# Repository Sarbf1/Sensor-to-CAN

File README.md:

# Sensor-to-CAN
A HAT for Arduino nano, to Connect nearly any sensor and send its walues using CAN or NMEA bus

This is an early version. The hardware is drwan, but not checked or tested.
The four layer board is slightly larger than the arduino nano R4, as i have added a shield ring (in case of use in high EMV areas such as in electric vehicles).

Also the code has not been written yet, but will follow.

The goal is to have a HAT board for on a Arduino Nano R4, that can connect to any sensor (3.3V 500mA, 5V 1A or Vin).
The sensor vaule (any voltage, or current input, selectable with a jumper) is processed by the arduino R4 and the sent using CANbus, using NMEA2000 protocol.
It has three LEDs that can be configured (currentls intended to show TX, RX and Erros) and two buttons, of wich one is used as Arduino Reset.

## next steps
- [ ] build and test prototype
- [ ] Prgram Arduino R4
- [ ] implement CAN and NMEA200
- [ ] create Bill of material
- [ ] Make second physical prototype

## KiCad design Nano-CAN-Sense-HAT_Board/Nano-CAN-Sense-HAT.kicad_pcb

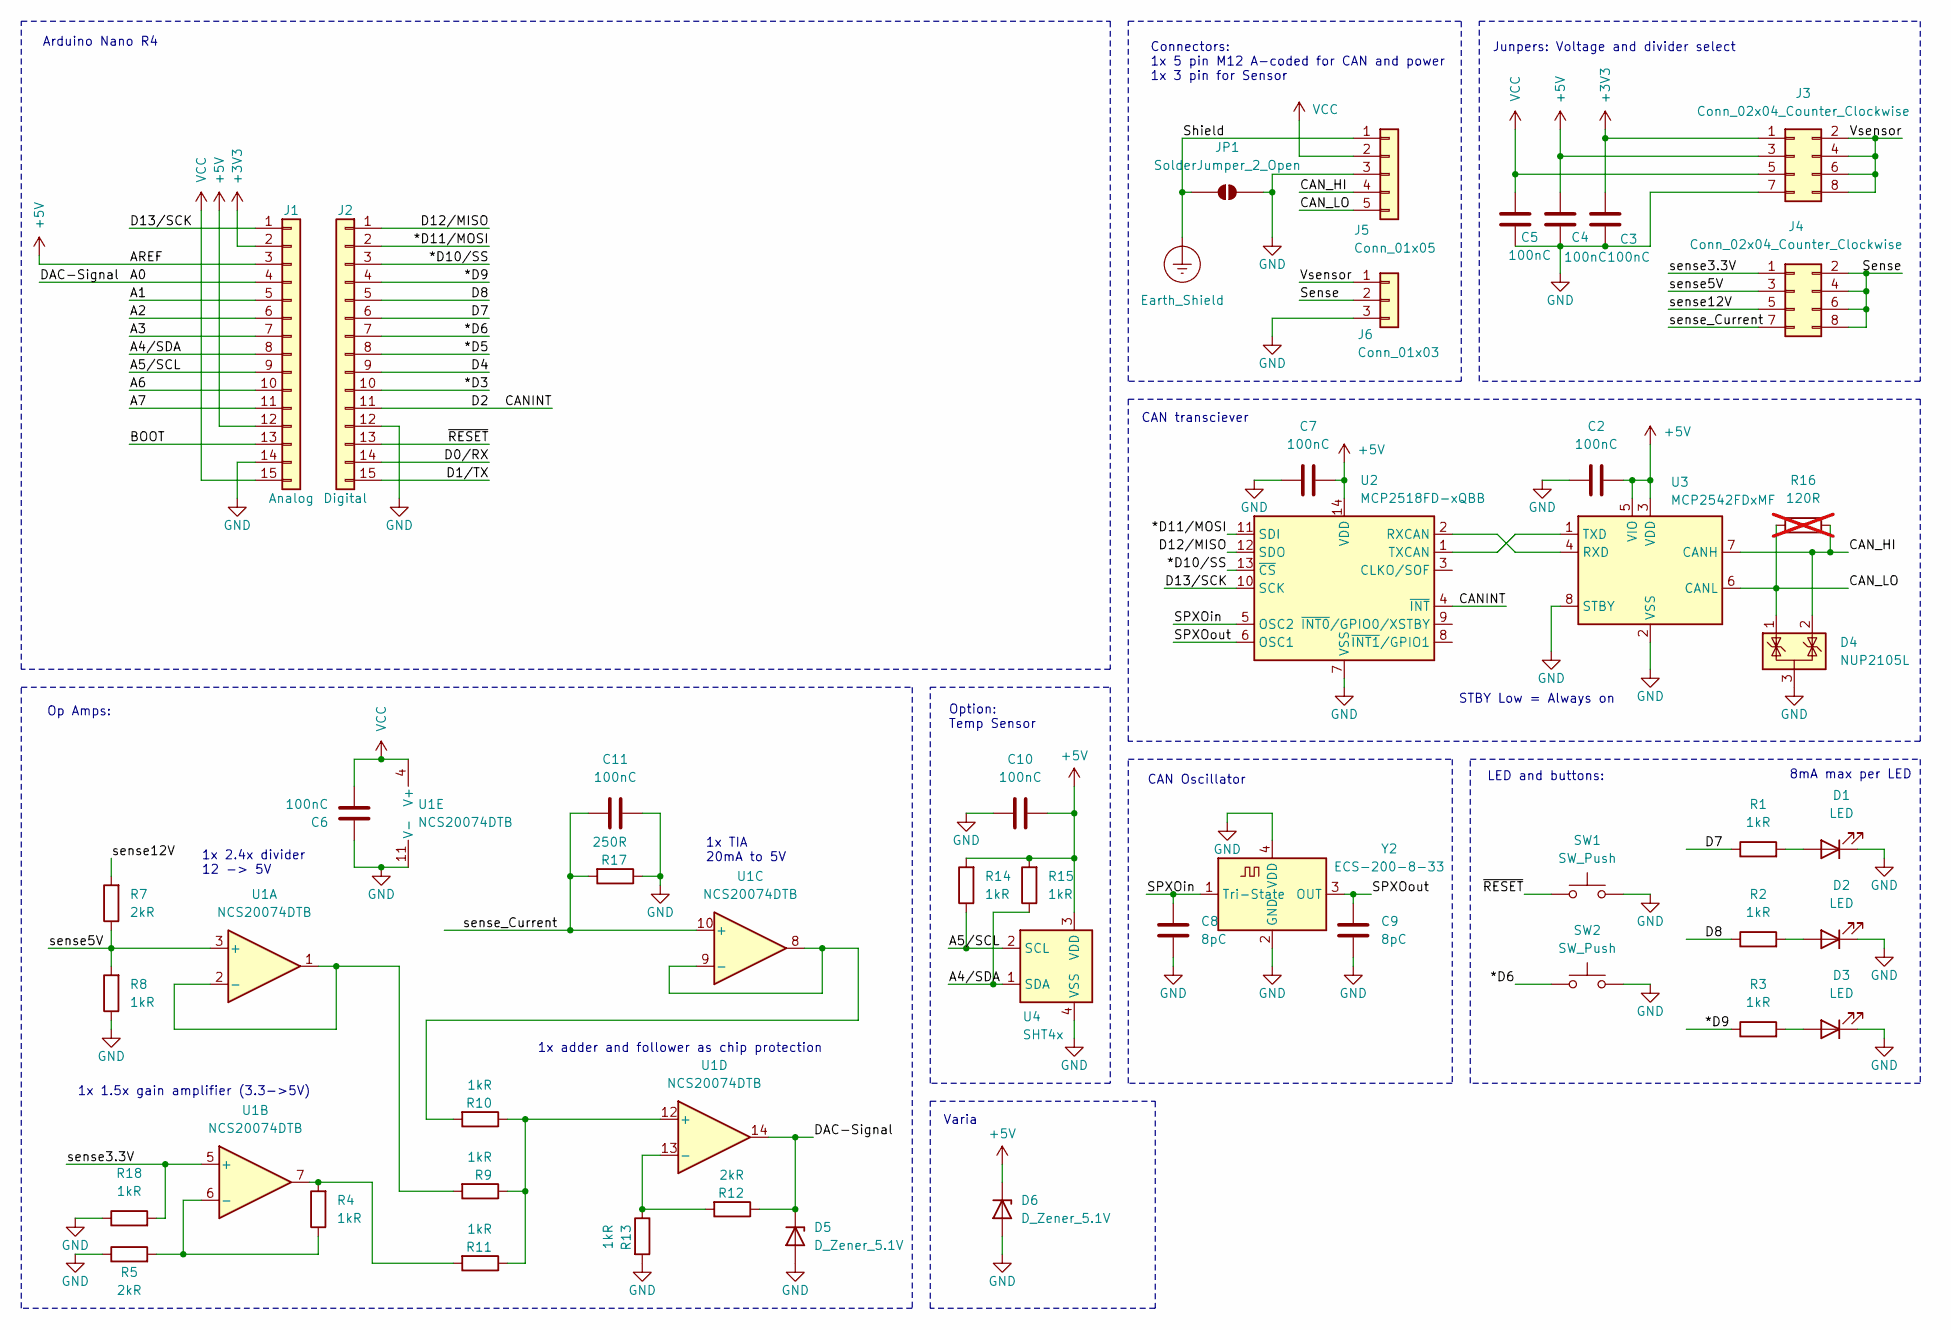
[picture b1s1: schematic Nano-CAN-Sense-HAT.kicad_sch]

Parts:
C2, C3, C4, C5, C6, C7, C10, C11: 100nC; C_0603_1608Metric
C8, C9: 8pC; C_0603_1608Metric
D1, D2, D3: LED; LED_0805_2012Metric
D4: NUP2105L; SOT-23
D5, D6: D_Zener_5.1V; D_SOD-323
J1: Analog; PinHeader_1x15_P2.54mm_Vertical
J2: Digital; PinHeader_1x15_P2.54mm_Vertical
J3, J4: Conn_02x04_Counter_Clockwise; PinHeader_2x04_P2.54mm_Vertical_SMD
J5: Conn_01x05; PinHeader_1x05_P2.54mm_Horizontal
J6: Conn_01x03; PinHeader_1x03_P2.54mm_Horizontal
JP1: SolderJumper_2_Open; SolderJumper-2_P1.3mm_Open_TrianglePad1.0x1.5mm
R1, R2, R3, R4, R8, R9, R10, R11, R13, R14, R15, R18: 1kR; R_0603_1608Metric
R5, R7, R12: 2kR; R_0603_1608Metric
R16: 120R; R_0603_1608Metric; not fitted
R17: 250R; R_0603_1608Metric
SW1, SW2: SW_Push; SW_SPST_B3U-1000P
U1: NCS20074DTB; TSSOP-14_4.4x5mm_P0.65mm
U2: MCP2518FD-xQBB; DFN-14-1EP_3x4.5mm_P0.65mm_EP1.65x4.25mm
U3: MCP2542FDxMF; DFN-8-1EP_3x3mm_P0.65mm_EP1.55x2.4mm
U4: SHT4x; Sensirion_DFN-4_1.5x1.5mm_P0.8mm_SHT4x_NoCentralPad
Y2: ECS-200-8-33; Oscillator_SMD_ECS_2520MV-xxx-xx-4Pin_2.5x2.0mm

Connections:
+3V3: C3.1, J1.2, J3.1
+5V: C2.2, C4.1, C7.2, C10.2, D6.1 (K), J1.3, J1.12, J3.3, R14.2, R15.2, U2.14 (VDD), U3.3 (VDD), U3.5 (VIO), U4.3 (VDD)
/*D3: J2.10
/*D5: J2.8
/*D6: J2.7, SW2.1
/*D9: J2.4, R3.1
/*D10/SS: J2.3, U2.13 (~CS)
/*D11/MOSI: J2.2, U2.11 (SDI)
/A0: D5.1 (K), J1.4, R12.1, U1.14
/A1: J1.5
/A2: J1.6
/A3: J1.7
/A4/SDA: J1.8, R15.1, U4.1 (SDA)
/A5/SCL: J1.9, R14.1, U4.2 (SCL)
/A6: J1.10
/A7: J1.11
/BOOT: J1.13
/CANINT: J2.11, U2.4 (~INT)
/CAN_HI: D4.2 (K), J5.4, R16.1, U3.7 (CANH)
/CAN_LO: D4.1 (K), J5.5, R16.2, U3.6 (CANL)
/D0/RX: J2.14
/D1/TX: J2.15
/D4: J2.9
/D7: J2.6, R1.1
/D8: J2.5, R2.1
/D12/MISO: J2.1, U2.12 (SDO)
/D13/SCK: J1.1, U2.10 (SCK)
/SPXOin: C8.2, U2.5 (OSC2), Y2.1 (Tri-State)
/SPXOout: C9.2, U2.6 (OSC1), Y2.3 (OUT)
/Sense: J4.2, J4.4, J4.6, J4.8, J6.2
/Vsensor: J3.2, J3.4, J3.6, J3.8, J6.1
/sense3.3V: J4.1, R18.2, U1.5 (+)
/sense5V: J4.3, R7.1, R8.2, U1.3 (+)
/sense12V: J4.5, R7.2
/sense_Current: C11.1, J4.7, R17.2, U1.10 (+)
/~RESET: J2.13, SW1.1
Earth_Shield: J5.1, JP1.1 (A)
GND: C2.1, C3.2, C4.2, C5.2, C6.2, C7.1, C8.1, C9.1, C10.1, C11.2, D1.1 (K), D2.1 (K), D3.1 (K), D4.3 (A), D5.2 (A), D6.2 (A), J1.14, J2.12, J3.7, J5.3, J6.3, JP1.2 (B), R5.1, R8.1, R13.2, R17.1, R18.1, SW1.2, SW2.2, U1.11 (V-), U2.7 (VSS), U2.15 (VSS), U3.2 (VSS), U3.8 (STBY), U3.9 (VSS), U4.4 (VSS), Y2.2 (GND), Y2.4 (VDD)
unnamed: D1.2 (A), R1.2
unnamed: D2.2 (A), R2.2
unnamed: D3.2 (A), R3.2
unnamed: R4.2, R11.2, U1.7
unnamed: R9.2, U1.1, U1.2 (-)
unnamed: R4.1, R5.2, U1.6 (-)
unnamed: R10.2, U1.8, U1.9 (-)
unnamed: R9.1, R10.1, R11.1, U1.12 (+)
unnamed: R12.2, R13.1, U1.13 (-)
unnamed: U2.2 (RXCAN), U3.4 (RXD)
unnamed: U2.1 (TXCAN), U3.1 (TXD)
VCC: C5.1, C6.1, J1.15, J3.5, J5.2, U1.4 (V+)

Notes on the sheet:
1x TIA 20mA to 5V
Junpers: Voltage and divider select
8mA max per LED
CAN Oscillator
Op Amps:
Arduino Nano R4
CAN transciever
1x 2.4x divider 12 -> 5V
Connectors: 1x 5 pin M12 A-coded for CAN and power 1x 3 pin for Sensor
STBY Low = Always on
LED and buttons:
1x adder and follower as chip protection
1x 1.5x gain amplifier (3.3->5V)
Varia
Option: Temp Sensor

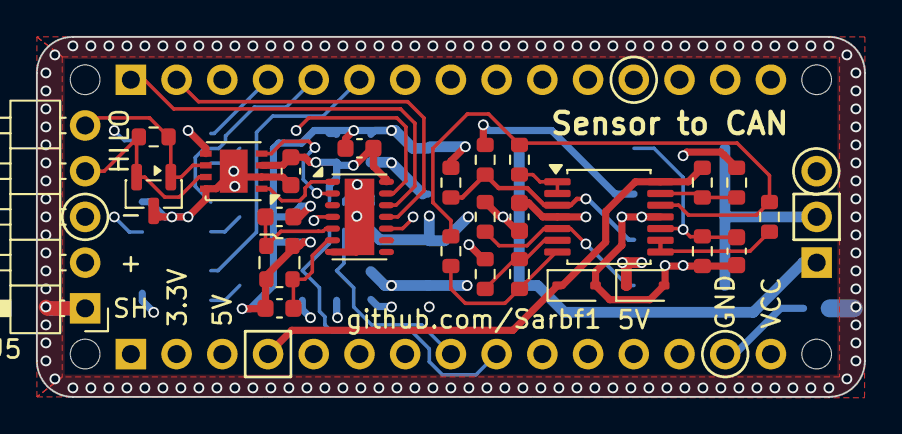
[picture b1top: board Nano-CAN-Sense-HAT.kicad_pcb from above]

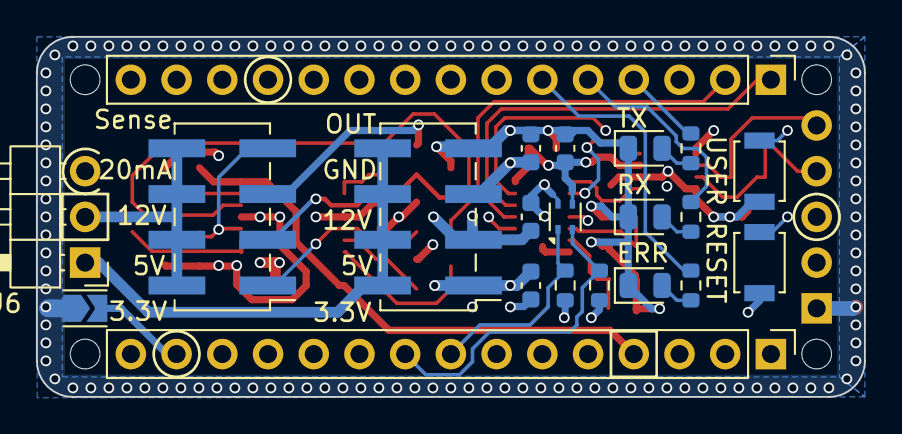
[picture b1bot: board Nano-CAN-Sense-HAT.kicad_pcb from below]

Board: 4 copper layers, 46.0 x 20.0 mm, 51 parts (21 on the bottom side), 39 nets.

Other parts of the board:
MH1, MH2, MH3, MH4: MountingHole_65mil

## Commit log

2026-04-09 added pdf and Screenshots
2026-04-09 minor
    Changes image folder structure, Improved Readme, and Added license
2026-04-18 Improved Can for CAN-FD
2026-04-19 Added images, and Readme
2026-04-19 added files and pictures
2026-04-19 Added license
2026-04-19 added .history to gitignore
2026-04-19 Added Temp sensor SHT4x, rounded board edge
2026-04-19 added Schematic as PDF for quick inspection without Kicad
2026-04-19 Changed oscillator, improved GND layout
2026-04-21 Added BOM, defined footprints
2026-04-23 Rodone all rounting, changed to 4-layer baord
2026-04-27 Minor board changes, cosmetics, new pictures
2026-04-28 power distribution using copper pours Gitignore *.zip
2026-04-29 aestethics, improved lables
2026-04-29 new images
2026-05-06 Started draft coding Layout fixes
2026-05-14 Changed OpAmp, improved lables
2026-05-17 Opamp supply 12V, Added Zener for protection
2026-05-19 Improved lables, better 5V protection diode, new images
